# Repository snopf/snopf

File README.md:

# Snopf USB password token

> Info: The password creation algorithm for Snopf has been fundamentally changed since 6b1df42b0c21d2e936d6018c70f1937114251a39. The new firmware and the new tools and account table files aren't compatible with the former version. The command line tool has been deprecated. Snopf also switched from using a 128 bit secret to using a 256 bit secret on the device. For upgrading the firmware you can use the firmware updater from the bootloader repository [here](https://github.com/Snopf/Snopf_bootloader). For installation and configuration follow this readme.

## What is Snopf?

Snopf is a very simple, yet effective and easy to use USB password tool. The Snopf USB device creates a unique and strong password for every service from the same 256 bit secret which never leaves the token.

Whenever Snopf is plugged into the computer you can make a password request and then the red LED will light up. If you press the button within 10 seconds Snopf will imitate a keyboard and type the password for the requested service.

Snopf is designed as a hardware-based password generator to tackle the security issues most commonly encountered with stored passwords on ordinary PCs, such as reading of password files by malware or browser exploits. It generates passwords deterministically from a securely kept master secret unaccessible to software running on the host. 

For more details on security and how it works, see the section *Security considerations* and *Operation principle* below.
Instructions on how to build your own are found in the section *Hardware* and *Building the Firmware and Host Software*. A short manual on how to use Snopf after you installed the software is found in *How to use it*.

## Advantages of Snopf

* Very simple and robust design
* Easy to use
* You don't have to remember any passwords anymore (except preferably a master PIN for Snopf)
* Every password is unique and as strong as the accessed service allows
* The actual password creation is only happening on the USB device
* It is (under certain restrictions) possible to restore all passwords from a 24 word mnemonic representing the 256 bit secret
* It's more secure than a common pure software based password manager because the password creation is physically detached from the computer
* As Snopf emulates a regular keyboard, no passwords are stored in the clipboard

### Advantage over Common Software Password Managers
Common software password managers are very good tools to create and manage strong passwords for all your logins. Still, there is a possibility of your computer being remotely attacked and an attacker is able to access your password database getting all your login credentials.
Snopf is an improvement over these managers because an attacker can't access your Snopf token remotely. All passwords are derived from the secret on the device which an attacker must have phyiscal access to. So there is an additional *physical barrier* for an attacker.

## Using Snopf
A default request process for a password is pictured below, using the Snopf browser extension:

To use Snopf two tools are currently available (an additional Android App is being developed), the *Snopf Manager* and a browser extension.

The Snopf Manager needs to be running on a computer when using Snopf. Beside managing the account table for snopf (see below) it also runs a background server for the browser extension. Whenever a password request is made in the browser, it is sent to the server which in turn talks to the USB device. The Snopf Manager minimizes to tray and runs silently in the background if you are not currently editing the account table. You can also create new entries in the account table from the browser extension.

### Account table
With Snopf Manager you can create new entries, delete entries and change entries in the account table. A Snopf account table is a simple json with entries for every unique (service, account) combination. Each entry has six fields:

1. `Service` = Hostname or service name for the login, for example the email service `examplemail.com`
2. `Account` = Your account at this service, for example the email address for the email service `my_mail_address@examplemail.com`
3. `Password length` = The password length you set for this service
4. `Password iteration` = An integer for every unique (service, account) combination which you increase if you have to set a new password for this combination for example after a databreach at the used service.
5. `Rules` = Rules for password creation, for example 'The password must include a lowercase character'
6. `Keymap` = A keymap which will be used for the password creation which allows to include and exclude certain characters

The account table file is AES encrypted on the hard disk using the same master password (not to be confused with the secret on the USB device!) that is used whenever a password request is submitted.

#### Setting the secret
You can change the secret on the Snopf device using Snopf Manager.

## Restoring passwords

To restore passwords, for example after losing or damaging Snopf, you need to be in possesion of the following data:

1. The Snopf's secret (comfortably as a 24 word mnemonic)
2. The optional master password (if you used one)
3. The account table

You might not absolutely need the account table if you have your logins, like email address and email service in your memory and just used passwords with default settings. Even if you need to remember *password iteration* you can just try out low numbers there.

Apart from that it is strongly advised to backup the account table and use a master password that you can remember. You should write down the 24 word mnemonic for the Snopf secret and store at a safe place.

With the above information you will be able to recreate all your passwords.

## Security considerations
Snopf isn't 100 % secure and a certain tradeoff between security, usability and economics has been made. Make sure to use Snopf only with your own or trusted PCs. It is also assumed that an adversary does not come into physical possesion of your Snopf. However, in case Snopf gets lost or is stolen, a reasonable safe master passphrase (the two-factor authentication approach) will still fend off or at least slow the attacker, depending on the strength of this passphrase.

Snopf has not been designed or further analyzed vs. more advanced attacks such as power analysis or timing side-channel attacks and could be theoretically vulnerable to either. Attacks of this and similar kinds are deemed outside the scope of the threat model that Snopf defends against. So far, regular computers don't seem to allow detailed current measurement at their USB ports which could potentially be used for remote attacks. More sophisticated attacks such as relying on analyzing the microcontroller's electromagnetic emissions are not deemed a common threat.
Timing attacks are similarly not expected to be a huge issue. The SHA256 crypto primitive used by Snopf runs in constant time. The iterated hashing to yield a password matching "password_valid" will cause some timing variation for a minority of passworts. However, as Snopf relies on a *manual* button press for replying with the password, a large amount of noise is added and makes analyses along this line a lot less feasible.

The ATtiny85 does not include a secure enclave (or similar) and reading out the microcontroller might be possible if an attacker has physical access. It can be made harder by setting the lockbits for the AVR but a capable attacker will be able to access the EEPROM data (where the secret is stored) eventually. A reasonable safe master passphrase will still prevent logins by an attacker at least for some time to create new passwords.

Passwords typed in by Snopf can of course still be intercepted by a keylogger and might land in the RAM and swap memory of the host where malware might access them. Covering those attack vectors is likewise out of scope for Snopf.
 
## Password Creation Algorithm
The password creation algorithm is explained in-depth [here](readme/password_algo.pdf).

## Hardware
You can find a KiCad project for Snopf in the `hardware` subfolder and also a PDF of the current schematic [here](https://github.com/Snopf/Snopf/blob/master/readme/schematic.pdf). The KiCad project also includes a PCB layout for a SMD version.

Bill of materials for the SMD version:
* ATTINY85-20SU SO(1)
* Resistor 10k 0603 (1)
* Resistor 220R 0603 (1)
* Resistor 1k 0603 (1)
* Resistor 1k5 0603 (1)
* Resistor 68R 0603 (2)
* Capacitor 18pF 0603 (2)
* Capacitor 100n 0603 (1)
* Capacitor 4u7 0805 (1)
* Crystal 12 Mhz 4 Pin (1)
* LED red 0603 (1)
* USB connector (1)
* Zener Diode 3,6V Mini Melf (2)
* Button Panasonic EVQQ2 (1)

There are links for Mouser parts that work for the PCB layout to be found in the KiCad schematic.

## Casing
A 3D printable casing can be found at `hardware/casing` both as a FreeCAD file and as four STEP files (bottom, top, button and a cap for the USB plug). The button is designed as a silicone button so that the diffuse LED light can been seen through it.
The dimensions of the casing are 41.9 x 19.4 x 11 mm.

## Running and building the Snopf software

### Python Venv
To avoid bugs and conflicts due to different versions of installed python packages it is advised to initialize a Python virtual enviroment for all operations described in this section. This includes running the python code as well as building binaries for either the AVR or the PC. Alternatively you can have a look at `src/py_requirements.txt` to see which Python packages and which versions are used for Snopf and install them accordingly.
To create a Python Venv you can simpy run
```
$ ./setup_py_env.sh
```
in the Linux console and
```
$ ./setup_py_env.ps1
```
in the Windows PowerShell. This will create a `.venv` directory with all necessary packages installed and activate that virtual enviroment for the current session.
To activate the virtual enviroment for the current session you run
```
$ source .venv/bin/activate
```
in the Linux console and
```
$ ./.venv/scripts/activate.ps1
```
in the Windows PowerShell.

### Linux udev rule
There is an udev rule for allowing USB acces to Snopf located in `src/host` which you can copy to `/etc/udev/rules.d` or you can simply run
```
$ ./install_usb_rule.sh
```

### Building the Firmware
You can compile the AVR code and program the AVR using the standard GNU toolchain using
```
$ make program
```
in the avr source directory `src/avr`. You'll probably have to alter the `Makefile` for your kind of programmer.

There also exists a bootloader written for this project, you can find it here [Snopf bootloader](https://github.com/Snopf/Snopf_bootloader) so that you can update the code on the device via USB. The bootloader is not necessary but it comes in handy for updating the firmware.

### Running the Snopf Manager Python code
After activating the Python virtual enviroment you can run the QT app as a Python script by running
```
python snopf.py
```
in `src/host/pc`.

### Building Snopf Manager Binaries for Linux
You can build a stand-alone binary for Snopf using PyInstaller. Just run `make` in `src/host/pc`.
It is advised to run `make` in the Python virtual enviroment to ensure that all needed packages are installed using the correct version.
The output will be created in `src/host/dist`.

### Building Snopf Manager Binaries for Windows
You can build an executable for Windows using the same Makefile as for Linux. You will have to have [GNU make for Windows](http://gnuwin32.sourceforge.net/packages/make.htm) installed. All scripts are written for PowerShell so you have to run Make from PowerShell.
PyInstaller will look for an [UPX](https://upx.github.io/) installation at `3rdparty/upx/`. You can create the binaries with or without using UPX compression.

### Browser extension
The firefox extension is located at `src/host/browser_extension` and can be packed into a zip file suitable for the browser by simply running `make` there.

There doesn't exist a signed version for the firefox browser extension yet so to permanently install the addon you would have to change the firefox settings  explictly to allow the installation of unsigned addons.
If you know what you are doing you can do this (for most firefox versions) by opening the 
```
about:config
```
page and set the value for 
```
xpinstall.signatures.required to false.
```
After doing that you can install the zip file under *about:addons*. If you change the setting back to *true* the addon will be deactivated by firefox.

Alternatively you can also temporarily install the addon by entering
```
about:debugging#/runtime/this-firefox
```
into the adress bar and and clicking *Load Temporary Add-on...*.

### Android App
An Android App is in development for the new Snopf algorithm.
<!-- 
The Android App is located at `src/host/android` as an project for `androidstudio` and can be build and applied to an Android phone using the same.
 -->

## Disclaimer
There is no warranty for data security and integrity or security issues of any kind. Care has been taken to make this a device that increases your security, however security bugs are possible.

You are free to use it and copy it but it comes **without any guarantees**.

## Links

* Snopf makes use of the excellent [V-USB driver](https://www.obdev.at/products/vusb/index.html)
* Article about Snopf on [Hackaday](https://hackaday.com/tag/snopf/)

## License
All code and schematics / hardware layouts are licensed under GNU General Public License (GPL) Version 2, see file License.txt.

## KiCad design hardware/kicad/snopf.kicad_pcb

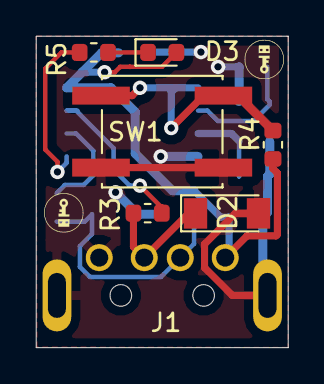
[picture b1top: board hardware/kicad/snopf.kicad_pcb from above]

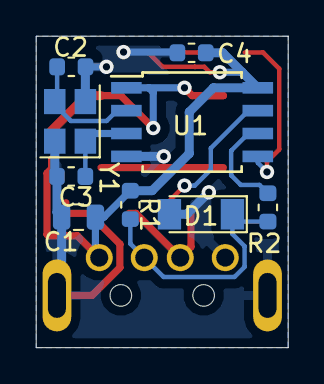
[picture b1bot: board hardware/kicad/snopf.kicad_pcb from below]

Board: 2 copper layers, 14.0 x 17.3 mm, 16 parts (9 on the bottom side), 11 nets.

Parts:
C1: 4u7; C_0805_2012Metric
C2, C3: 18pF; C_0603_1608Metric
C4: 100n; C_0603_1608Metric
D1, D2: Z3,6V; D_MiniMELF
D3: User LED; LED_0603_1608Metric
J1: USB_A; USB_plug_UP2-AH
R1: 1k5; R_0603_1608Metric
R2, R3: 68R; R_0603_1608Metric
R4: 10k; R_0603_1608Metric
R5: 220R; R_0603_1608Metric
SW1: User Button; SW_SPST_EVQQ2
U1: ATTINY85-20SU; SOIJ-8_5.3x5.3mm_P1.27mm
Y1: 12 MHz; Crystal_SMD_Abracon_ABM8G-4Pin_3.2x2.5mm

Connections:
D+: D2.1, J1.3, R3.2
D-: D1.1, J1.2, R1.2, R2.2
GND: C1.2, C2.1, C3.1, C4.2, D1.2, D2.2, J1.4, J1.5, SW1.2, U1.4, Y1.2, Y1.4
unnamed: D3.1, R5.1
PB0: R5.2, U1.5
PB1: R2.1, U1.6
PB2: R3.1, U1.7
PB5: R4.2, SW1.1, U1.1
VCC: C1.1, C4.1, D3.2, J1.1, R1.1, R4.1, U1.8
XTAL1: C2.2, U1.2, Y1.3
XTAL2: C3.2, U1.3, Y1.1

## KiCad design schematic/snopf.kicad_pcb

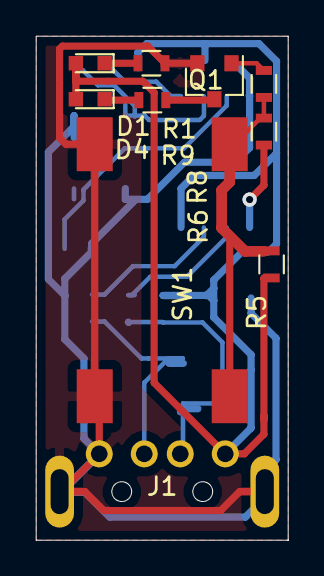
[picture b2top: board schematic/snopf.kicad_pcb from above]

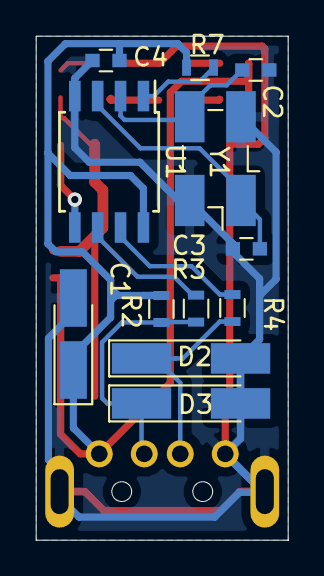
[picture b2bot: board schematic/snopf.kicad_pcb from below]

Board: 2 copper layers, 14.0 x 28.0 mm, 22 parts (12 on the bottom side), 15 nets.

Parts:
C1: 4u7; CP_Tantalum_Case-A_EIA-3216-18_Hand
C2, C3: 18pF; C_0603
C4: 100n; C_0603
D1: LED GREEN; LED_0603
D2, D3: Z3,6V; D_MiniMELF_Handsoldering
D4: LED RED; LED_0603
J1: USB_A; USB_A_male_4_5_pitch
Q1: 2N 2222A; SOT-23
R1, R9: 220R; R_0603
R2: 1k5; R_0603
R3, R4: 68R; R_0603
R5, R7, R8: 10k; R_0603
R6: 1k; R_0603
SW1: KMR 231 G LFS; button_schurter_1618_XX_gullwing
U1: ATTINY85-20SU; SOIJ-8_5.3x5.3mm_Pitch1.27mm
Y1: 12 MHz; Crystal_SMD_EuroQuartz_MJ-4pin_5.0x3.2mm_HandSoldering

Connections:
GND: C1.2, C2.2, C3.2, C4.2, D2.2, D3.2, J1.4, J1.5, Q1.2, R1.1, SW1.2, U1.4, Y1.2, Y1.4
unnamed: C2.1, U1.2, Y1.3
unnamed: C3.1, U1.3, Y1.1
unnamed: D1.1, R1.2
unnamed: D2.1, J1.3, R4.2
unnamed: D3.1, J1.2, R2.2, R3.2
unnamed: D4.1, R9.1
unnamed: Q1.1, R8.1
unnamed: Q1.3, R9.2
unnamed: R3.1, U1.6
unnamed: R4.1, U1.7
unnamed: R5.1, R6.1, R8.2, SW1.1
unnamed: R6.2, U1.5
unnamed: R7.1, U1.1
VCC: C1.1, C4.1, D1.2, D4.2, J1.1, R2.1, R5.2, R7.2, U1.8

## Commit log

2020-01-22 init
2020-01-22 Add schematic pdf to readme
2020-01-24 README: add link to obdev vusb
2020-01-30 add simple android app
2020-01-31 fix preselection of username in browser extension
2020-02-05 todo
2020-02-05 change python to python3 in Makefile tests
2020-02-05 create directory before installing native app
2020-02-05 create subdirectories for snopf_cmd, snopf_manager before installation
2020-02-05 create ~/.local/bin directory if nonexistent before installation
2020-02-05 initialize default options in browser extension
2020-02-06 Clarify command help
2020-02-06 remove non existent phony target
2020-02-06 repeat mnemonic after change_secret
2020-02-06 safeguards in install scripts to prevent running as root
2020-02-06 explicitly check if user is root for usb rule install
2020-02-06 add wheel to py requirements
2020-02-06 change text from ok to request
2020-02-06 select first tab in new entry dialog
2020-02-06 Use reset button as button input
2020-02-07 fix entry insertion from browser extension
    the browser driver assumed the account table to be unchanged
    since start which could lead to data loss if accounts had been
    inserted using other tools
2020-02-13 remove unnecessary variable
2020-02-13 formatting
2020-02-16 refactor z85 encoding
2020-02-24 fix setting password length + iteration in browser extension
2020-03-20 Add a 3D printable casing
2020-03-20 update todo
2020-04-16 Changed rules to work on Ubuntu and Arch Linux
2020-06-27 implement new password algorithm for avr and python/qt
    first implementation of the new snopf password algorithm for the
    usb device and a host qt application
2020-06-30 fix passphrase stuff in algo pdf
2020-06-30 Redesign browser extension to use websocket for native communication
2020-06-30 fix typo
2020-06-30 throw more specific exception
2020-06-30 add test for request messages
2020-06-30 adjust logging name
2020-06-30 create extra class for websocketserver
2020-07-01 add requirement for pytest-qt
2020-07-01 add tests for websocket server commands
2020-07-01 add extra widget for account table tree
2020-07-01 use new account table widget class in main application
2020-07-03 use constant for keymap length of 64
2020-07-03 move keymap edit to new class
2020-07-03 add tests
2020-07-03 remove unused imports
2020-07-03 refactor
2020-07-03 do not remove QT Network stuff after building
2020-07-04 don't do anything if no entry is selected
2020-07-04 redesign gui
2020-07-04 catch usb error for insufficient permissions
2020-07-04 close websocket after password request
2020-07-04 remove unused import
2020-07-05 fix comment field (was readonly)
2020-07-06 remove pkg-resources requirement
2020-07-06 add windows powershell script for virtualenv init
2020-07-06 import QtSvg explicitly
    scg icons won't work on windows if we don't import QtSvg
2020-07-12 Replace pyusb with hidapi when running windows
2020-07-12 ps script for git commit inserting
2020-07-12 windows makefile + scripts
2020-07-12 simplify makefile
2020-07-12 add .ico file
2020-07-12 add icon to pyinstaller
2020-07-12 fix clean target for windows
2020-07-12 add qtpdf to remove list
2020-07-12 add more unused libs to kill list
2020-07-13 update building/running section of readme
2020-07-13 add hackaday reference
2020-07-13 refactor buffer clearing
2020-07-13 refactor password request
2020-07-13 add check for feature report length
2020-07-13 replace vendor request with hid report when using libusb
2020-07-14 Implement simpler and easier USB communications
2020-07-14 fix device lifetime in set_secret_wizard for hidapi use
2020-07-14 adapt new usb messages to windows
2020-07-14 fix message lengths for windows
2020-07-14 fix avr testing usb_comm import
2020-07-14 fix text format for label for expected password
2020-07-14 fix link
2020-07-14 fix markdown
2020-07-14 typo
2020-07-15 fix websocket error connection
2020-07-15 raise timeout for windows tests
2020-07-15 fix test_usb_comm
2020-07-15 select item on single click under windows
2020-07-15 fix pyinstaller cleanup for windows
2020-07-15 change to onefile option for pyinstaller
2020-07-15 fix new entry creation after new account table creation
2020-07-15 remove deprecated todo
2020-07-16 use appdirs for config file and log files
2020-07-16 allow empty passphrase for account table
2020-07-16 add script for running snopf with local config file and log files
2020-07-16 don't fail when running outside of git repo
2020-07-16 use appdir to find default dir for saving account table
2020-07-16 add gitignore
2020-07-17 remove fixme
2020-07-17 add functionality for setting keyboard layout on usb device
2020-07-17 fix auto uppercase for validity check password field
2020-07-17 search in user-data-dir when opening files
2020-07-23 Use a TableModel for account table editing
2020-07-23 decrease delay to make button more responsive
2020-07-23 add success message box
2020-08-04 fix request for new entry from websocket client
2020-08-04 add standard qtmodeltester test
2020-08-05 refactor account table appending
2020-08-05 fix logger info
2020-08-05 activate saveAs menu action when account table is active
2020-08-05 fix newentry / deleted items order bug
2020-08-05 prohibit change of service and account column from mapper
2020-08-05 reset model when saving
2020-08-05 fix preset keymaps selection
2020-08-05 select tab 0 at start
2020-08-05 fix keymap_editing tests
2020-08-05 add test
2020-08-27 Add websocket client whitelisting
2020-08-27 update todos
2020-08-27 only run websocket server with active account table
2020-08-27 only show filename in window title
2020-08-27 remove unused code
2020-08-27 fix order of websocket / account table loading
    we need to have a websocket server available whenever we load
    the account table file
2021-04-20 Bump py from 1.8.1 to 1.10.0 in /src
    Bumps [py](https://github.com/pytest-dev/py) from 1.8.1 to 1.10.0.
    - [Release notes](https://github.com/pytest-dev/py/releases)
    - [Changelog](https://github.com/pytest-dev/py/blob/master/CHANGELOG.rst)
    - [Commits](https://github.com/pytest-dev/py/compare/1.8.1...1.10.0)
2021-06-11 Bump websockets from 8.1 to 9.1 in /src
    Bumps [websockets](https://github.com/aaugustin/websockets) from 8.1 to 9.1.
    - [Release notes](https://github.com/aaugustin/websockets/releases)
    - [Changelog](https://github.com/aaugustin/websockets/blob/9.1/docs/changelog.rst)
    - [Commits](https://github.com/aaugustin/websockets/compare/8.1...9.1)
    ---
    updated-dependencies:
